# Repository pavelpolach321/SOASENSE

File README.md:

# About this repository:

The code is in the src/ folder

Mode of operation can be controlled with microswitches on the top board.

position  function           LEFT                     RIGHT     Comment
[8]       wifi credentials   setup or use old setup   erase     Implemented
[7]       connectivity       wifi                     lorawan   Not implemented yet
[6]       display            on                       off       Not implemented yet
[5]       reserved           [x]                      [x]       Not implemented yet
[4]       serial debug       on                       off       Not implemented yet
[3]       serial output      text                     json      Not implemented yet
[2]       reserved           [x]                      [x]       Not implemented yet
[1]       reserved           [x]                      [x]       Not implemented yet

# Connect the node

* Toggle the on/off switch down.
* Connect the power cable
* To erase/reset wifi credentials, put the swqitch n.8 to the right
* Toggle the on/off switch up, the board will start and display will show MAC address and AP details. Previously saved wifi cponnection is erased. Node is ready to connect.
* Put the switch n.8 to the left and reset/re-power the node
* Check accessible AP points with your mobile, search for SOASENSE_AP
* Connect with password "tacrnode"
* Page should appear, if not, gGo to 192.168.0.4, setup wifi credentials where you want node to be conected
* Node will restart itself and start sending data. You can see counter and other details on display.

# Firmware files

For provisioning use files in node_setup/ and keyfiles/ folders

During normal fw compilation, EEPROM mode should be "#define EEPROM_MODE         EEPROM_SHOW"

All sensor's related files are in a folder src/hardware'

To disable/enable/control sensor's behaviour', check setup.h file.

Most of the functional code of LMIC-node stays the same, we just introduced a few function calls to collect data, create payload and write results into debug. Function related to our fork are in hardware.cpp/.h

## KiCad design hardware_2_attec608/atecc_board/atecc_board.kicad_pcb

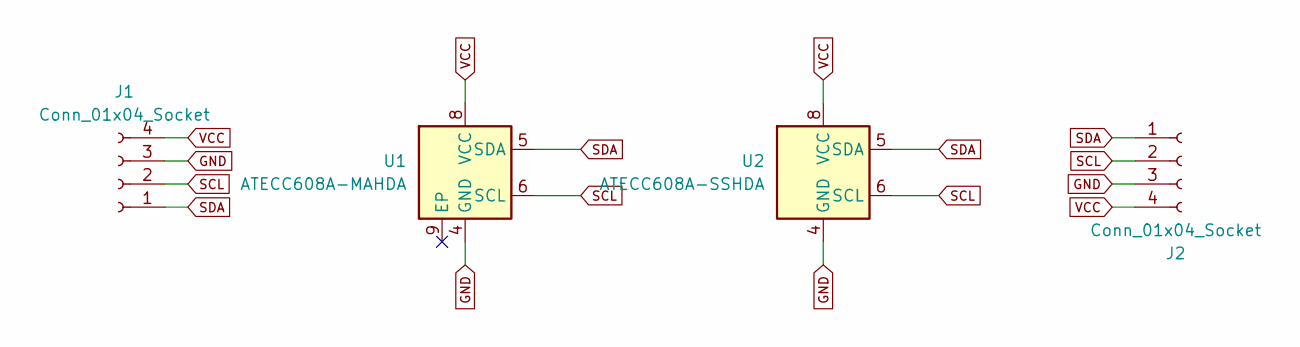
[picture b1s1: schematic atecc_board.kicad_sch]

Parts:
J1, J2: Conn_01x04_Socket; PinHeader_1x04_P2.54mm_Vertical
U1: ATECC608A-MAHDA; DFN-8-1EP_3x2mm_P0.5mm_EP1.3x1.5mm
U2: ATECC608A-SSHDA; SOIC-8_3.9x4.9mm_P1.27mm

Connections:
GND: J1.3, J2.3, U1.4 (GND), U2.4 (GND)
SCL: J1.2, J2.2, U1.6 (SCL), U2.6 (SCL)
SDA: J1.1, J2.1, U1.5 (SDA), U2.5 (SDA)
VCC: J1.4, J2.4, U1.8 (VCC), U2.8 (VCC)

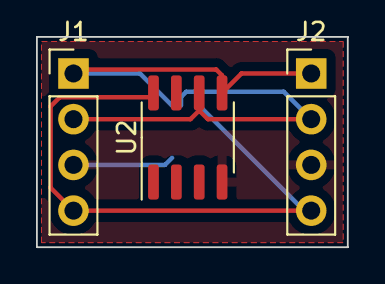
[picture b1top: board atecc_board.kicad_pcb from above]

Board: 2 copper layers, 17.3 x 11.7 mm, 4 parts (1 on the bottom side), 4 nets.

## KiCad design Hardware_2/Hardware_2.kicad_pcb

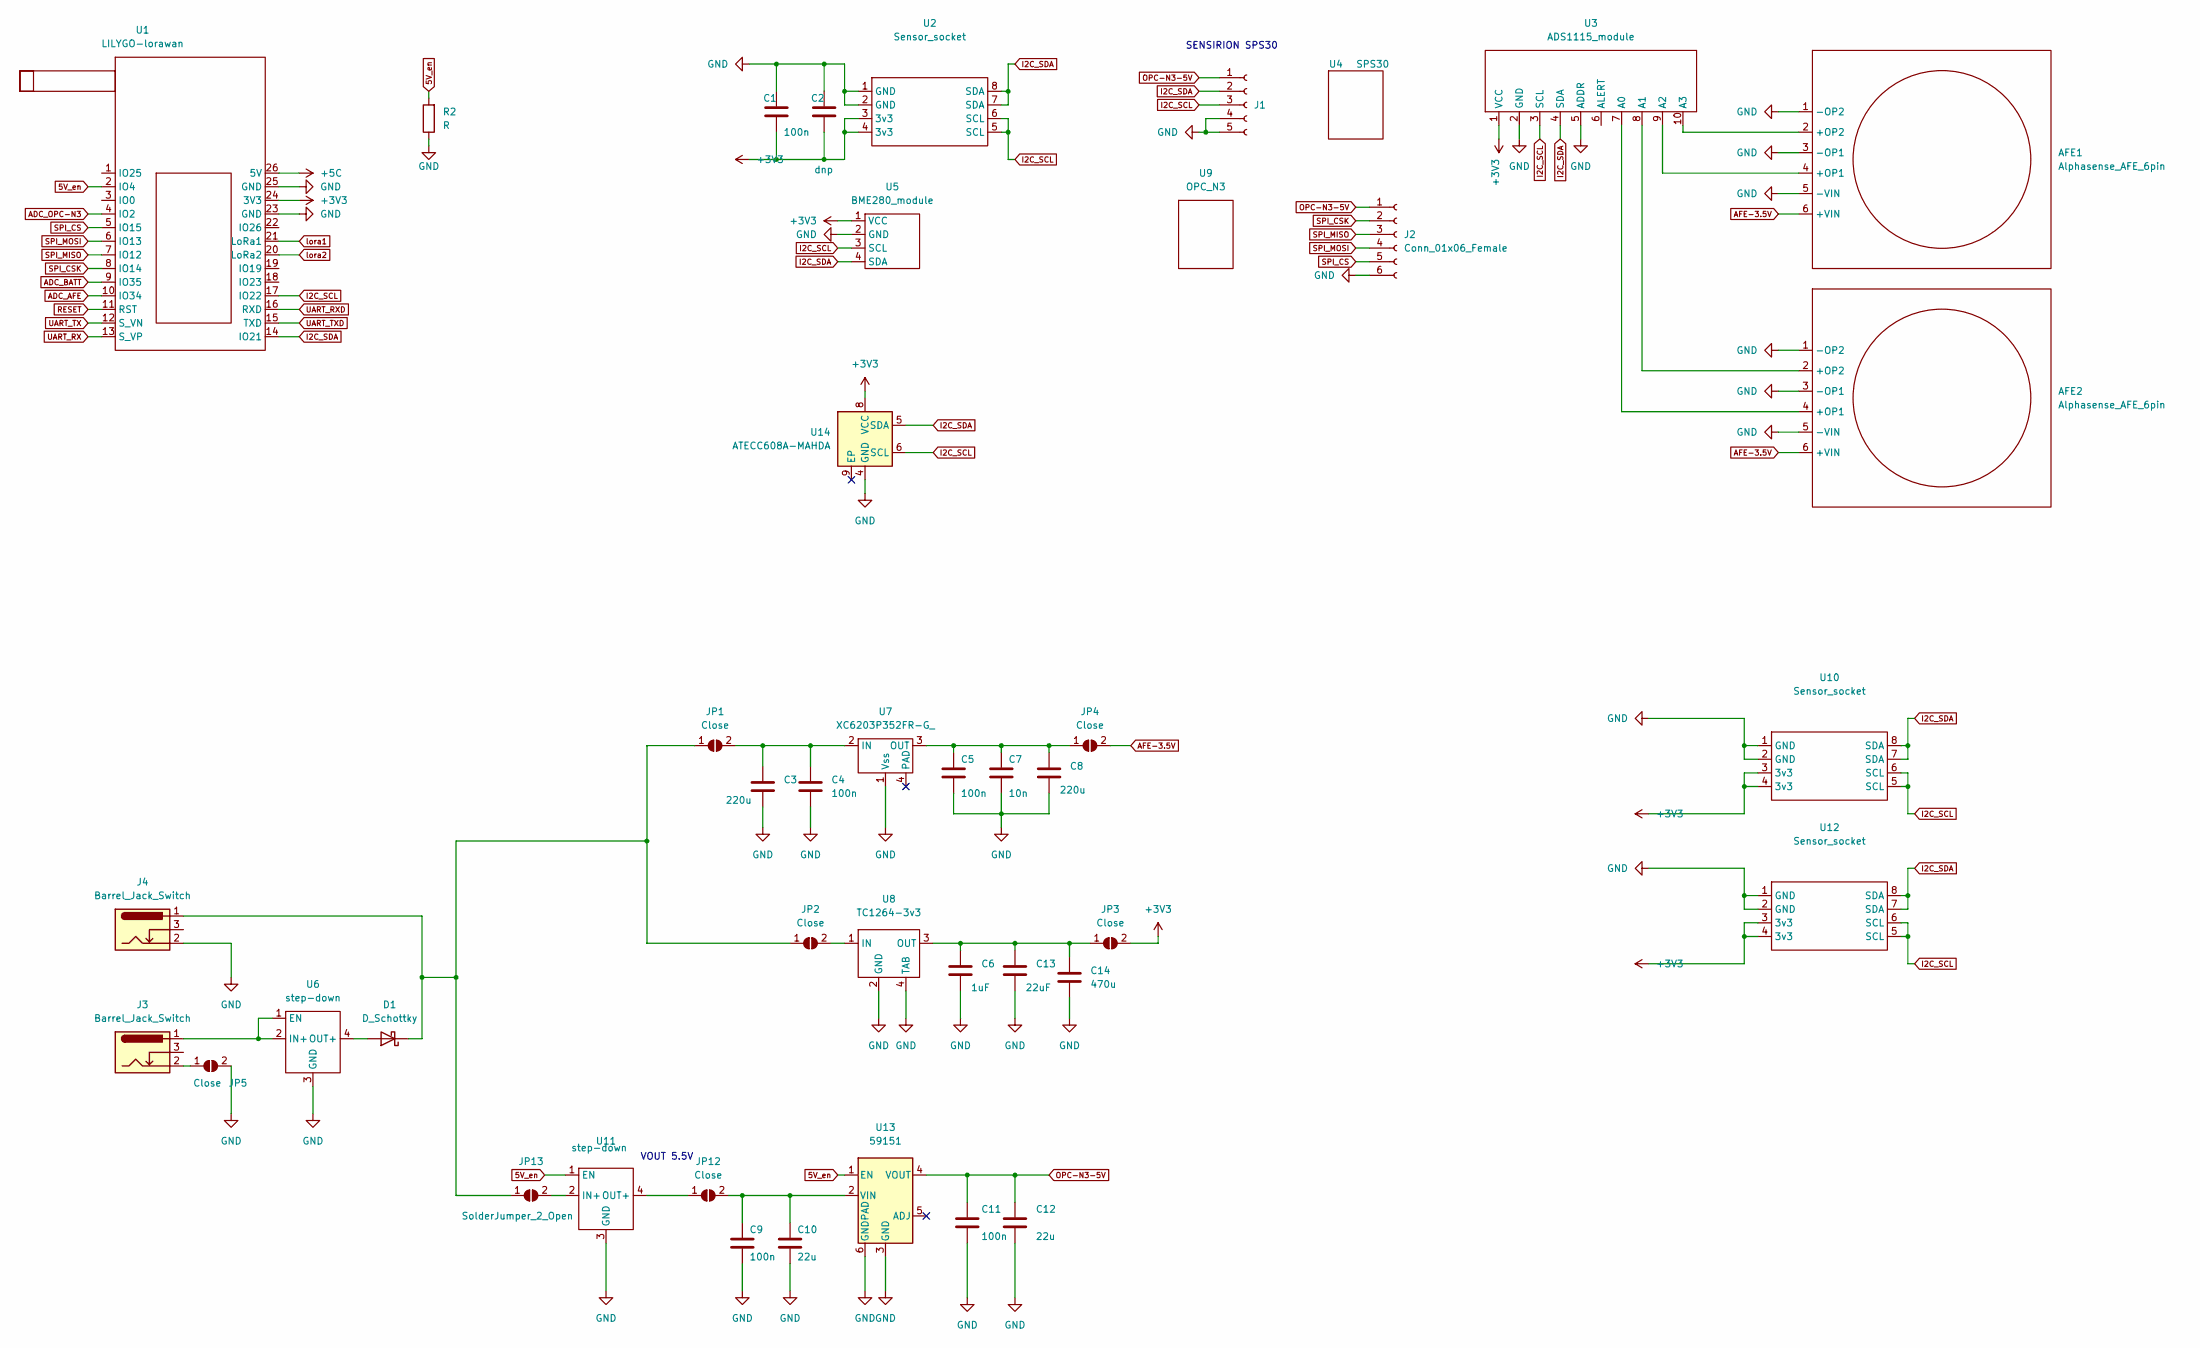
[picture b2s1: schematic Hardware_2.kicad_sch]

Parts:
AFE1: Alphasense_AFE_6pin; Alphasense_AFE_6pin-LEFT
AFE2: Alphasense_AFE_6pin; Alphasense_AFE_6pin-RIGHT
C1: 100n; C_0805_2012Metric_Pad1.18x1.45mm_HandSolder
C2: dnp; C_0805_2012Metric_Pad1.18x1.45mm_HandSolder
C3, C8: 220u; CP_Radial_D5.0mm_P2.50mm
C4, C5, C9, C11: 100n; C_0805_2012Metric
C6: 1uF; C_0805_2012Metric_Pad1.18x1.45mm_HandSolder
C7: 10n; C_0805_2012Metric
C10, C12: 22u; C_0805_2012Metric
C13: 22uF; C_0805_2012Metric_Pad1.18x1.45mm_HandSolder
C14: 470u; CP_Radial_D10.0mm_P3.50mm
D1: D_Schottky; D_2114_3652Metric_Pad1.85x3.75mm_HandSolder
J1: Conn_01x05_Female; PinHeader_1x05_P2.54mm_Vertical
J2: Conn_01x06_Female; PinHeader_1x06_P2.54mm_Vertical
J3, J4: Barrel_Jack_Switch; BarrelJack_Horizontal
JP1, JP2, JP3, JP4, JP12: Close; SolderJumper-2_P1.3mm_Bridged_RoundedPad1.0x1.5mm
JP5: Close; SolderJumper-2_P1.3mm_Bridged_Pad1.0x1.5mm
JP13: SolderJumper_2_Open; SolderJumper-2_P1.3mm_Bridged_RoundedPad1.0x1.5mm
R2: R; R_0805_2012Metric
U1: LILYGO-lorawan; LILYGO-LORAWAN
U2, U10, U12: Sensor_socket; Sensor_module
U3: ADS1115_module; ADS1115-module
U4: SPS30
U5: BME280_module; BME280-module
U6, U11: step-down; mp2315-module
U7: XC6203P352FR-G_; SOT-223
U8: TC1264-3v3; SOT-223
U9: OPC_N3; opc-n3_3holes
U13: 59151; PPAK
U14: ATECC608A-MAHDA; DFN-8-1EP_3x2mm_P0.5mm_EP1.3x1.5mm

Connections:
5V_en: R2.2, U1.2 (IO4), U11.1 (EN), U13.1 (EN)
+3V3: C1.2, C2.2, JP3.2 (B), U1.24 (3V3), U2.3 (3v3), U2.4 (3v3), U3.1 (VCC), U5.1 (VCC), U10.3 (3v3), U10.4 (3v3), U12.3 (3v3), U12.4 (3v3), U14.8 (VCC)
+5C: U1.26 (5V)
ADC_AFE: U1.10 (IO34)
ADC_BATT: U1.9 (IO35)
ADC_OPC-N3: U1.4 (IO2)
AFE-3.5V: AFE1.6 (+VIN), AFE2.6 (+VIN), JP4.2 (B)
GND: AFE1.1 (-OP2), AFE1.3 (-OP1), AFE1.5 (-VIN), AFE2.1 (-OP2), AFE2.3 (-OP1), AFE2.5 (-VIN), C1.1, C2.1, C3.2, C4.2, C5.2, C6.2, C7.2, C8.2, C9.2, C10.2, C11.2, C12.2, C13.2, C14.2, J1.4, J1.5, J2.6, J4.2, JP5.2 (B), R2.1, U1.23 (GND), U1.25 (GND), U2.1 (GND), U2.2 (GND), U3.2 (GND), U3.5 (ADDR), U5.2 (GND), U6.3 (GND), U7.1 (Vss), U8.2 (GND), U8.4 (TAB), U10.1 (GND), U10.2 (GND), U11.3 (GND), U12.1 (GND), U12.2 (GND), U13.3 (GND), U13.6 (GNDPAD), U14.4 (GND)
I2C_SCL: J1.3, U1.17 (IO22), U2.5 (SCL), U2.6 (SCL), U3.3 (SCL), U5.3 (SCL), U10.5 (SCL), U10.6 (SCL), U12.5 (SCL), U12.6 (SCL), U14.6 (SCL)
I2C_SDA: J1.2, U1.14 (IO21), U2.7 (SDA), U2.8 (SDA), U3.4 (SDA), U5.4 (SDA), U10.7 (SDA), U10.8 (SDA), U12.7 (SDA), U12.8 (SDA), U14.5 (SDA)
unnamed: AFE1.4 (+OP1), U3.9 (A2)
unnamed: AFE1.2 (+OP2), U3.10 (A3)
unnamed: AFE2.4 (+OP1), U3.7 (A0)
unnamed: AFE2.2 (+OP2), U3.8 (A1)
unnamed: D1.2 (A), U6.4 (OUT+)
unnamed: D1.1 (K), J4.1, JP1.1 (A), JP2.1 (A), JP13.1 (A)
unnamed: C3.1, C4.1, JP1.2 (B), U7.2 (IN)
unnamed: JP2.2 (B), U8.1 (IN)
unnamed: C6.1, C13.1, C14.1, JP3.1 (A), U8.3 (OUT)
unnamed: C5.1, C7.1, C8.1, JP4.1 (A), U7.3 (OUT)
unnamed: J3.2, JP5.1 (A)
unnamed: JP12.1 (A), U11.4 (OUT+)
unnamed: C9.1, C10.1, JP12.2 (B), U13.2 (VIN)
unnamed: JP13.2 (B), U11.2 (IN+)
unnamed: J3.1, U6.1 (EN), U6.2 (IN+)
OPC-N3-5V: C11.1, C12.1, J1.1, J2.1, U13.4 (VOUT)
RESET: U1.11 (RST)
SPI_CS: J2.5, U1.5 (IO15)
SPI_CSK: J2.2, U1.8 (IO14)
SPI_MISO: J2.3, U1.7 (IO12)
SPI_MOSI: J2.4, U1.6 (IO13)
UART_RX: U1.13 (S_VP)
UART_RXD: U1.16 (RXD)
UART_TX: U1.12 (S_VN)
UART_TXD: U1.15 (TXD)
lora1: U1.21 (LoRa1)
lora2: U1.20 (LoRa2)

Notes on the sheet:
VOUT 5.5V
SENSIRION SPS30

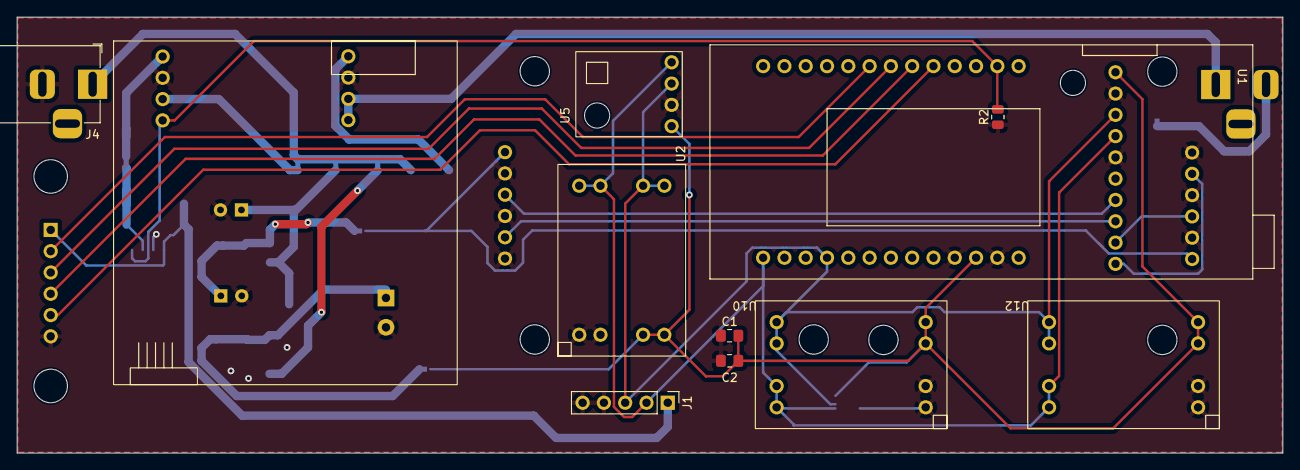
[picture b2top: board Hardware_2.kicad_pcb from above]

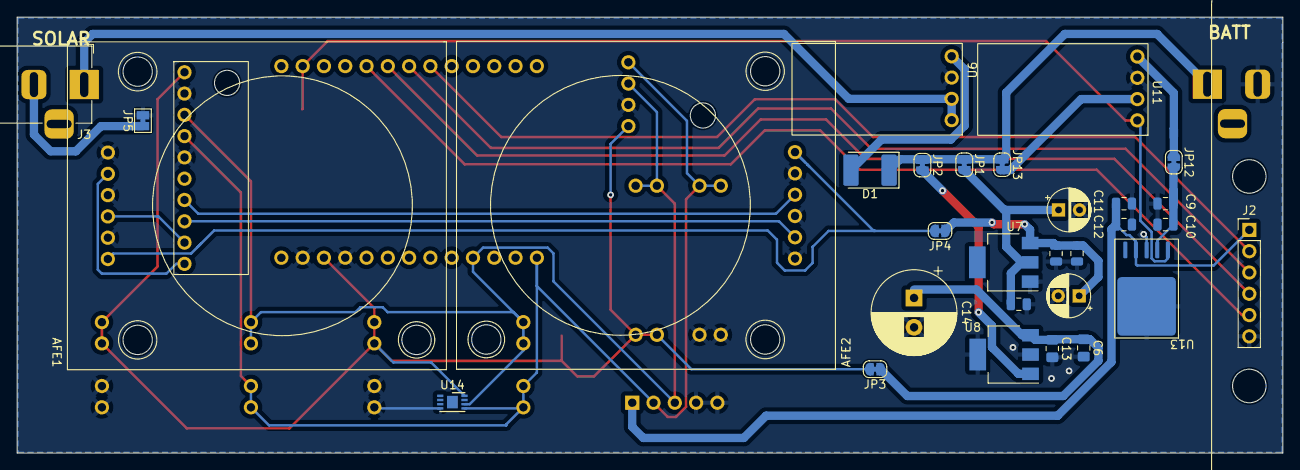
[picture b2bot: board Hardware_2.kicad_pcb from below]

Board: 2 copper layers, 151.0 x 52.0 mm, 43 parts (32 on the bottom side), 26 nets.
